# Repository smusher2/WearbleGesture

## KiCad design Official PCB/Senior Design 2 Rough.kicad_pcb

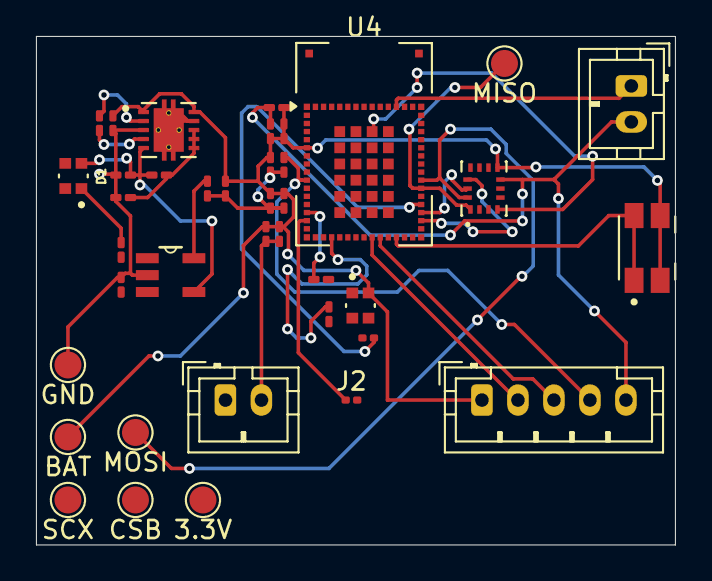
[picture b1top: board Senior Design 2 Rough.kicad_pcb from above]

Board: 2 copper layers, 35.5 x 28.2 mm, 39 parts (0 on the bottom side), 24 nets.

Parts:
3.3V: TestPoint; TestPoint_Pad_D1.5mm
BAT: TestPoint; TestPoint_Pad_D1.5mm
C1, C4: 4.7uF; C_0201_0603Metric_Pad0.64x0.40mm_HandSolder
C2: 0.1uF; C_0201_0603Metric_Pad0.64x0.40mm_HandSolder
C3, C5: 10uF; C_0201_0603Metric_Pad0.64x0.40mm_HandSolder
C6: 10u; C_0201_0603Metric_Pad0.64x0.40mm_HandSolder
C7, C8, C9, C13: 100n; C_0201_0603Metric_Pad0.64x0.40mm_HandSolder
C10: 10n; C_0201_0603Metric_Pad0.64x0.40mm_HandSolder
C11, C12: 1u; C_0201_0603Metric_Pad0.64x0.40mm_HandSolder
CSB: TestPoint; TestPoint_Pad_D1.5mm
D1: LED; LED_EAST1616RGBA3
D3: EAST1616RGBA3; LED_EAST1616RGBA3
FB1: 120R; R_0201_0603Metric_Pad0.64x0.40mm_HandSolder
GND: TestPoint; TestPoint_Pad_D1.5mm
J1, J5: Conn_01x02; JST_PH_B2B-PH-K_1x02_P2.00mm_Vertical
J2: Conn_02x01; R_0201_0603Metric
J4: Conn_01x05; JST_PH_B5B-PH-K_1x05_P2.00mm_Vertical
L1: 2.2uH; L_0201_0603Metric_Pad0.64x0.40mm_HandSolder
MISO: TestPoint; TestPoint_Pad_D1.5mm
MOSI: TestPoint; TestPoint_Pad_D1.5mm
R1: 100; R_0201_0603Metric_Pad0.64x0.40mm_HandSolder
R2: 2k; R_0201_0603Metric_Pad0.64x0.40mm_HandSolder
R3: 470; R_0201_0603Metric_Pad0.64x0.40mm_HandSolder
R4: 78; R_0201_0603Metric_Pad0.64x0.40mm_HandSolder
R5: 112; R_0201_0603Metric_Pad0.64x0.40mm_HandSolder
R6: 112; R_0201_0603Metric
S1: EVQ-P7A01P; SW_EVQ-P7A01P
SCX: TestPoint; TestPoint_Pad_D1.5mm
U1: TPS63001; VREG_V62_16624-01YE
U2: MCP73831T-2ACI_OT; SOT95P280X145-5N
U3: BMI323; XDCR_BMI270
U4: STM32WB5MMG; ST-SiP-LGA-86-11x7.3mm

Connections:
+3.3V: BAT.1, C3.1, C5.1, C6.1, C7.1, C8.1, C9.1, C10.1, C11.1, C12.1, D3.3, FB1.1, FB1.2, J2.2, J4.1, S1.2_1, S1.2_2, U1.1 (VOUT), U1.10 (FB), U3.8 (VDD), U4.6 (VDDA)
/Haptic Motor: J5.1, U4.50 (PA8)
/SPI2 MISO: MISO.1, U3.1 (SDO), U4.37 (PB14)
/SPI2 MOSI: MOSI.1, U3.14 (SDX), U4.38 (PB15)
/SWCLK: J4.3, U4.26 (PA14)
/SWDIO: J4.2, U4.25 (PA13)
/Switch: S1.1_1, S1.1_2, U4.28 (PA10)
GND: C1.2, C2.2, C3.2, C4.2, C5.2, C6.2, C7.2, C8.2, C9.2, C10.2, C11.2, C12.2, C13.2, GND.1, J1.2, J4.5, J5.2, R2.2, U1.3 (PGND), U1.9 (GND), U1.11 (PGND), U2.2 (VSS), U3.7 (GND)
unnamed: D1.1 (K), R3.1
unnamed: C4.1, J1.1, U2.3 (VBAT)
unnamed: 3.3V.1, J2.1, U4.15 (VBAT)
unnamed: C13.1, J4.4, U4.10 (NRST)
unnamed: C2.1, R1.2, U1.6 (EN), U1.7 (PS/SYNC), U1.8 (VINA)
unnamed: L1.1, U1.4 (L1)
unnamed: L1.2, U1.2 (L2)
unnamed: R2.1, U2.5 (PROG)
unnamed: R3.2, U2.1 (STAT)
unnamed: U3.12 (CSB), U4.33 (PD0)
unnamed: U3.4 (INT1), U4.75 (PD8)
unnamed: U3.13 (SCX), U4.34 (PD1)
unnamed: R5.1, U4.20 (PB4)
unnamed: R4.1, U4.14 (PB8)
unnamed: R6.1, U4.35 (PB13)
VDD: C1.1, D1.2 (A), R1.1, U1.5 (VIN), U2.4 (VDD)

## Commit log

2025-10-15 Disable shake detection for tap event handling
    Commented out shake detection logic in bmi_323.c.
2025-10-16 Change timestamp increment from 30 to 50 ms
    Updated timestamp increment for UART transmission.
2025-10-21 Refactor main.c for gesture detection and tap handling
    Merged and refactored main.c for improved gesture detection and tap handling.
2025-10-21 Refactor BMI323 driver for improved tap detection
    Refactor BMI323 driver with enhanced comments and tuning parameters for tap detection. Adjusted feature engine settings and improved code clarity.
2025-10-21 Modify BMI323_HandleTapEvent return type and add TAP_3
    Changed the return type of BMI323_HandleTapEvent to const char* and added TAP_3 definition.
2025-10-23 Update threshold and gyro gate parameters
2025-10-23 Refactor gesture label printing logic
    Removed unused printing helper and simplified gesture label printing logic.
2025-10-23 Refactor gesture detection logic and add grace window
    Refactor gesture detection code to improve clarity and functionality. Introduce same-direction grace window for gesture detection, update threshold handling, and enhance comments.
2025-10-28 inital commit
2025-10-28 core folder
2025-10-28 add STM32_WPAN
2025-10-28 init commit desktop app
2025-10-28 add core
2025-10-30 Update gesture detection and add raw data streaming
    Merged gesture detection and UART printing updates. Added raw acceleration/gyroscope streaming every 50 ms.
2025-11-04 add main and p2p
2025-12-10 Add gesture recognition application with BMI323
    This file implements a gesture recognition application using the BMI323 sensor. It includes initialization, data handling, and gesture processing with UART output.
2025-12-10 Add gesture detection and tap handling functionality
    This file implements gesture detection and tap handling using the BMI323 IMU sensor. It includes configuration, data processing, and UART communication for gesture recognition.
